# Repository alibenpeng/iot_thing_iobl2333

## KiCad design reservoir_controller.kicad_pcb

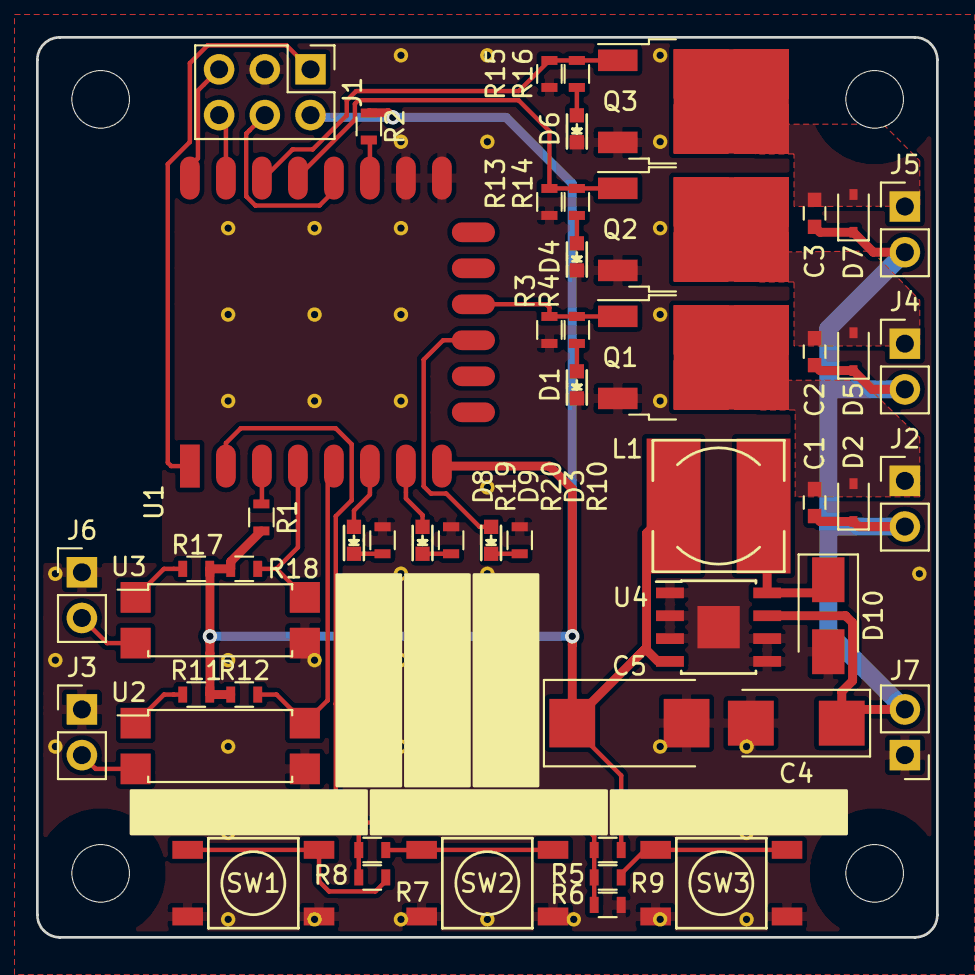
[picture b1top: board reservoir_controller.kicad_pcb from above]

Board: 2 copper layers, 50.0 x 50.0 mm, 57 parts (0 on the bottom side), 35 nets.

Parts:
C1, C2, C3: 100n; C_0603
C4: 68uF; CP_Tantalum_Case-C_EIA-6032-28_Reflow
C5: 120uF; CP_Tantalum_Case-D_EIA-7343-31_Reflow
D1, D3, D4, D6, D8, D9: LED; LED-0603
D2, D5, D7: 1N4148; D_SOD-323
D10: 1N5817; D_SMA
J1: ESP UART; Pin_Header_Straight_2x03_Pitch2.54mm
J2, J4, J5: Conn_01x02; Pin_Header_Straight_1x02_Pitch2.54mm
J3, J6: Level Input; Pin_Header_Straight_1x02_Pitch2.54mm
J7: Conn_01x02-conn; Pin_Header_Straight_1x02_Pitch2.54mm
L1: 100uH; Choke_SMD_7.3x7.3_H4.5
M1, M2, M3, M4: MOUNTING_HOLE; MountingHole_3.2mm_M3
Q1, Q2, Q3: QM3006D; TO-252-2
R1, R2, R3, R12, R13, R15, R18: 10k; R_0603
R4, R10, R11, R14, R16, R17, R19, R20: 330; R_0603
R5: 12k; R_0603
R6, R9: 4k7; R_0603
R7: 1R; R_0603
R8: 1k; R_0603
SW1, SW2, SW3: SW_PUSH; BUTTON_5.1
U1: ESP-12E
U2, U3: PC817; SO-4_7.6x3.6mm_Pitch2.54mm
U4: LM2594HVM-3.3; SOIC-8-1EP_3.9x4.9mm_Pitch1.27mm

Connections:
+3V3: C5.1, J1.2, L1.1, R1.2, R2.1, R5.1, R11.1, R12.1, R17.1, R18.1, U1.8, U4.4
+12V: C1.1, C2.1, C3.1, C4.1, D2.1, D5.1, D7.1, J2.2, J4.2, J5.2, J7.2, U4.7
/ESP-12E/ESP_ADC: R5.2, R6.1, R7.2, R8.2, R9.2, U1.2
/ESP-12E/ESP_GPIO4: Q2.1, R13.1, R14.1, U1.19
/ESP-12E/ESP_GPIO5: Q3.1, R15.1, R16.1, U1.20
/ESP-12E/ESP_GPIO9: D3.2, U1.11
/ESP-12E/ESP_GPIO10: Q1.1, R3.1, R4.1, U1.12
/ESP-12E/ESP_GPIO12: D8.2, U1.6
/ESP-12E/ESP_GPIO13: D9.2, U1.7
/ESP-12E/ESP_GPIO14: R12.2, U1.5, U2.4
/ESP-12E/ESP_GPIO16: R18.2, U1.4, U3.4
/ESP-12E/ESP_RXD: J1.6, U1.21
/ESP-12E/ESP_TXD: J1.5, U1.22
/ESP-12E/gpio0: J1.4, U1.18
/ESP-12E/reset: J1.1, U1.1
GND: C4.2, C5.2, D1.1, D4.1, D6.1, D10.2, J1.3, J3.1, J6.1, J7.1, Q1.3, Q2.3, Q3.3, R3.2, R6.2, R10.2, R13.2, R15.2, R19.2, R20.2, SW1.2, SW2.2, SW3.2, U1.15, U1.16, U2.3, U3.3, U4.1, U4.2, U4.3, U4.5, U4.6, U4.9
unnamed: C1.2, D2.2, J2.1, Q1.2
unnamed: C2.2, D5.2, J4.1, Q2.2
unnamed: C3.2, D7.2, J5.1, Q3.2
unnamed: D1.2, R4.2
unnamed: D3.1, R10.1
unnamed: D4.2, R14.2
unnamed: D6.2, R16.2
unnamed: D8.1, R19.1
unnamed: D9.1, R20.1
unnamed: D10.1, L1.2, U4.8
unnamed: J3.2, U2.2
unnamed: J6.2, U3.2
unnamed: R1.1, U1.3
unnamed: R2.2, U1.17
unnamed: R7.1, SW1.1
unnamed: R8.1, SW2.1
unnamed: R9.1, SW3.1
unnamed: R11.2, U2.1
unnamed: R17.2, U3.1

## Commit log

2020-04-16 not sure what happened
